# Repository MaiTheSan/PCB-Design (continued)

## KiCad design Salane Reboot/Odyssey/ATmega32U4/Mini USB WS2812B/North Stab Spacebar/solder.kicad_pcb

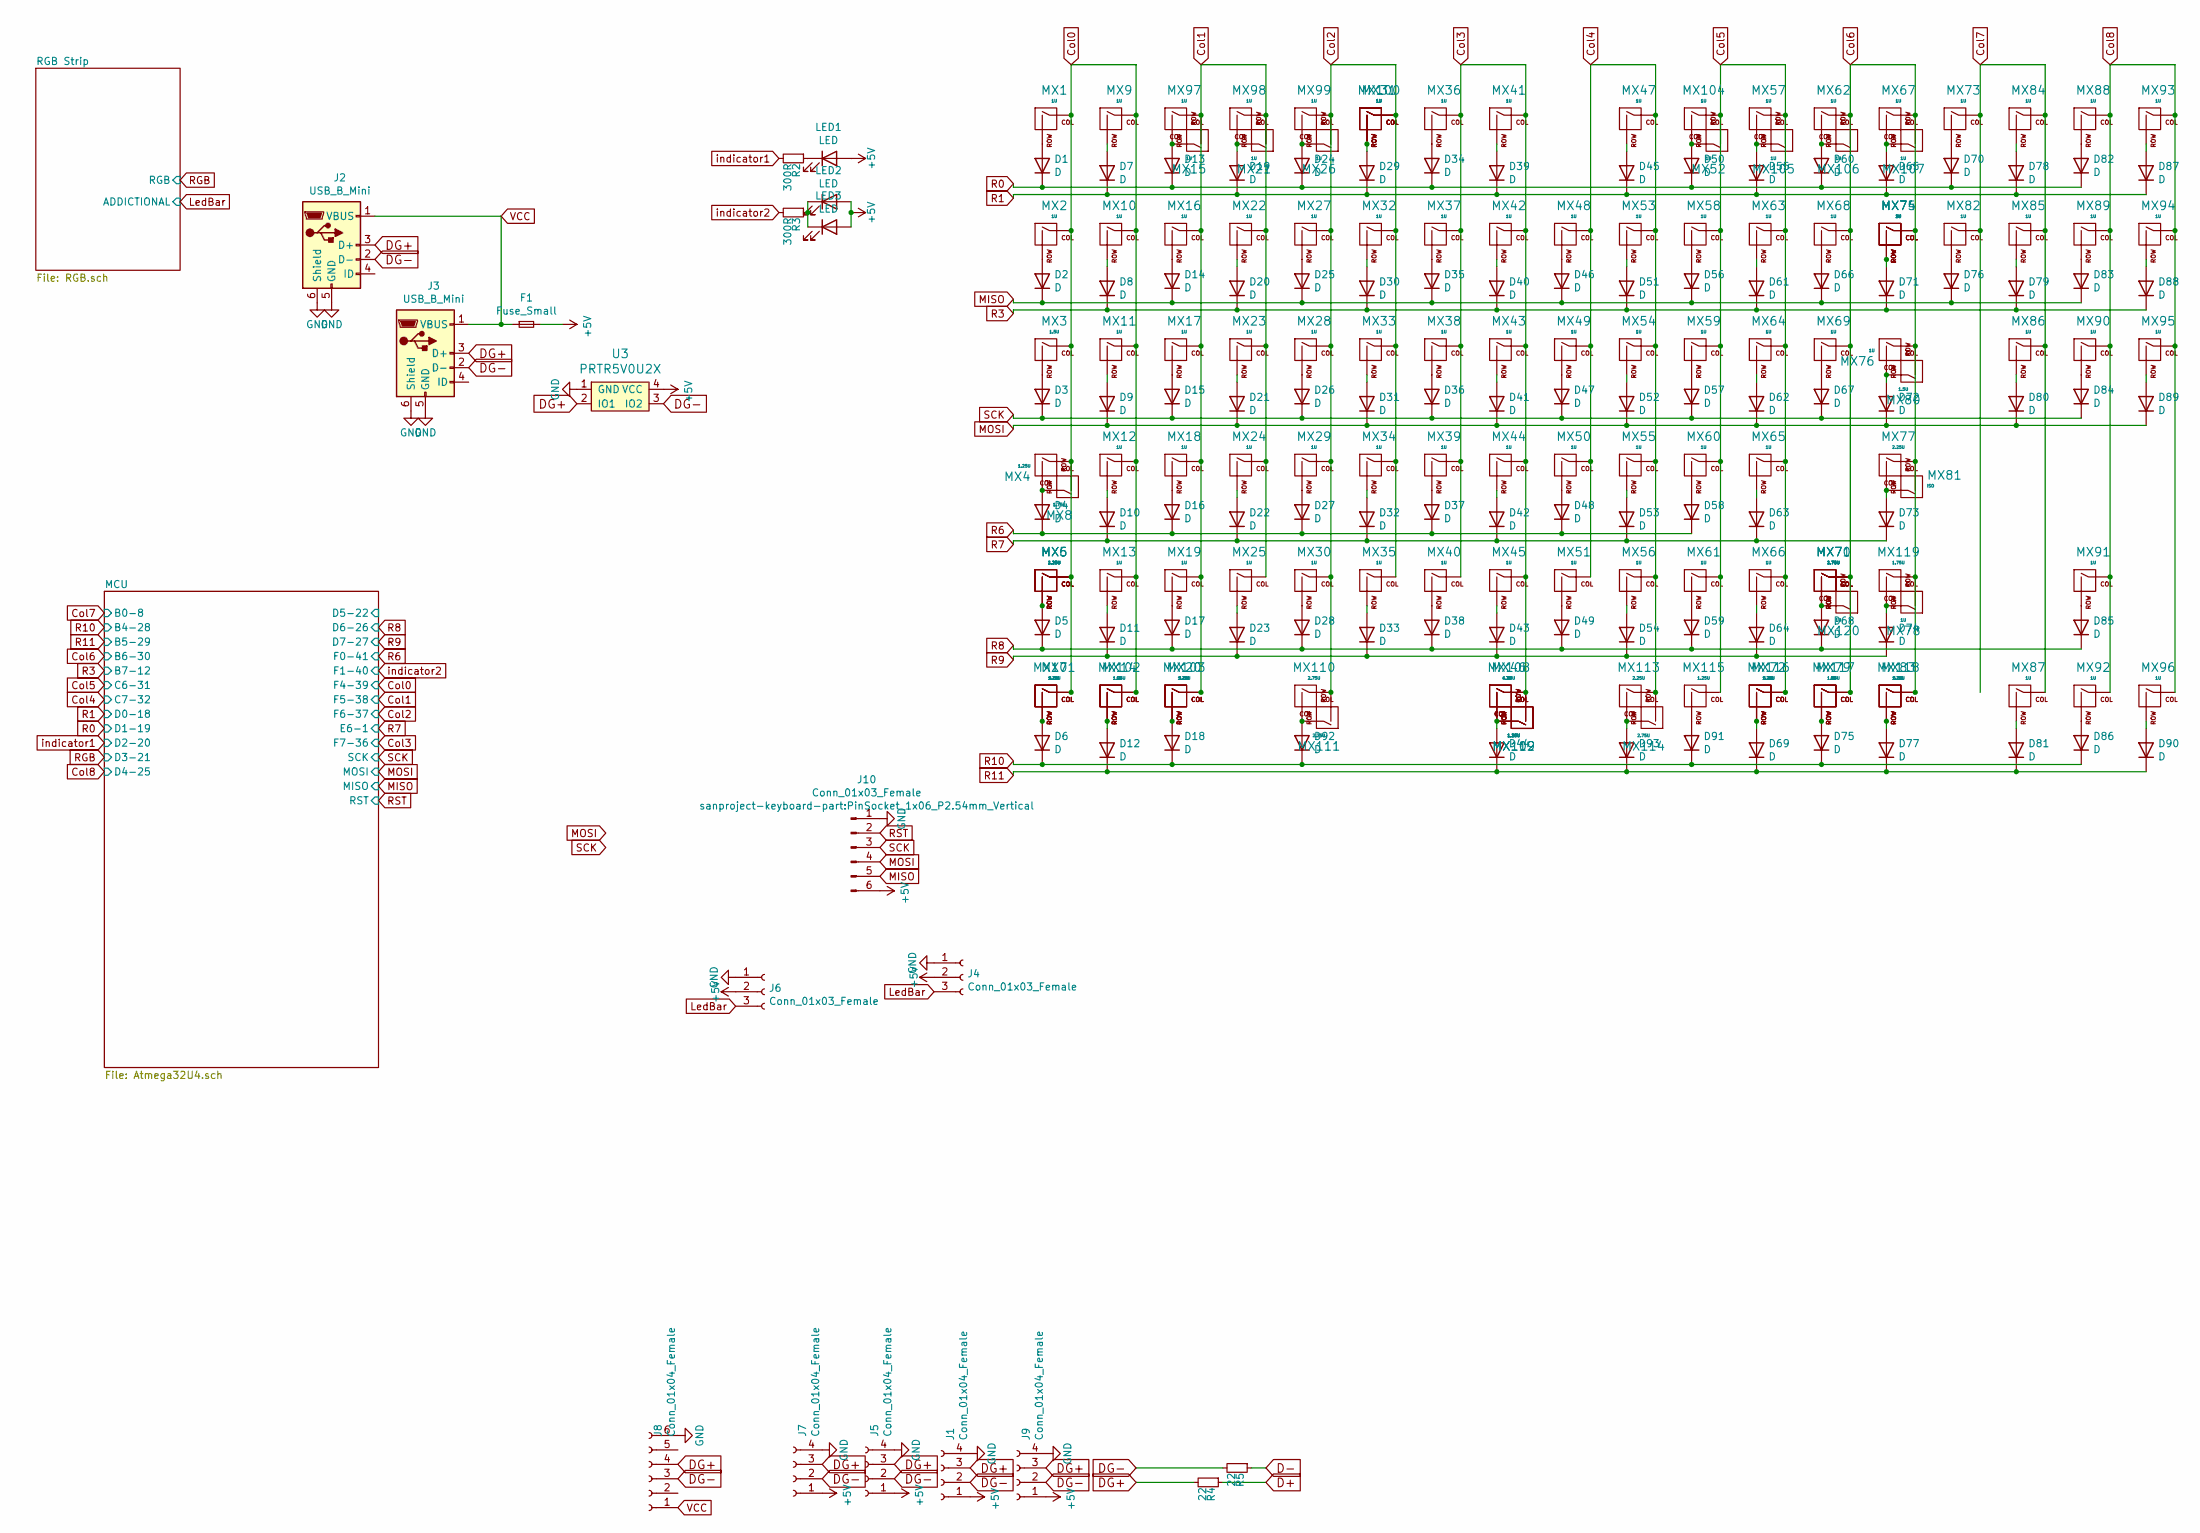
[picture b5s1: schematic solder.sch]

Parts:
D1, D2, D3, D4, D5, D6, D7, D8, D9, D10, D11, D12, D13, D14, D15, D16, D17, D18, D19, D20, D21, D22, D23, D24, D25, D26, D27, D28, D29, D30, D31, D32, D33, D34, D35, D36, D37, D38, D39, D40, D41, D42, D43, D44, D45, D46, D47, D48, D49, D50, D51, D52, D53, D54, D55, D56, D57, D58, D59, D60, D61, D62, D63, D64, D65, D66, D67, D68, D69, D70, D71, D72, D73, D74, D75, D76, D77, D78, D79, D80, D81, D82, D83, D84, D85, D86, D87, D88, D89, D90, D91, D92, D93: D; DIODE_1206_SawnsProjects
F1: Fuse_Small; Fuse_SMD1206_Reflow
J1, J7, J9: Conn_01x04_Female; JST-SR-4
J2, J3: USB_B_Mini; Molex-0548190589
J4: Conn_01x03_Female; PinSocket_1x03_P2.54mm_Vertical
J5: Conn_01x04_Female; PinHeader_1x04_P1.27mm_Vertical
J6: Conn_01x03_Female; JST-SR-3
J8: Conn_01x04_Female; BreakoutUSB
J10: Conn_01x03_Female; PinSocket_1x06_P2.54mm_Vertical
LED1, LED3: LED; MXOnly-LEDONLY-FLIPPED
LED2: LED; MXOnly-LEDONLY
MX1, MX2, MX9, MX10, MX11, MX12, MX13, MX14, MX15, MX16, MX17, MX18, MX19, MX21, MX22, MX23, MX24, MX25, MX26, MX27, MX28, MX29, MX30, MX31, MX32, MX33, MX34, MX35, MX36, MX37, MX38, MX39, MX40, MX41, MX42, MX43, MX44, MX45, MX47, MX48, MX49, MX50, MX51, MX52, MX53, MX54, MX55, MX56, MX57, MX58, MX59, MX60, MX61, MX62, MX63, MX64, MX65, MX66, MX67, MX68, MX69, MX73, MX74, MX76, MX78, MX79, MX82, MX84, MX85, MX86, MX87, MX88, MX89, MX90, MX91, MX92, MX93, MX94, MX95, MX96, MX97, MX98, MX99, MX100, MX104, MX105, MX106, MX107, MX120: 1U; MXOnly-1U-NoLED
MX3, MX7, MX20, MX72, MX80, MX83: 1.5U; MXOnly-1.5U-NoLED
MX4, MX5, MX101, MX102, MX103, MX109, MX112, MX115, MX116, MX117, MX118: 1.25U; MXOnly-1.25U-NoLED
MX6: 2.25U; MXOnly-2.25U-NoLED
MX8, MX70, MX119: 1.75U; MXOnly-1.75U-NoLED
MX46: 7U; MXOnly-7U-ReversedStabilizers-NoLED
MX71: 2.75U; MXOnly-2.75U-NoLED
MX75: 2U; MXOnly-2U-NoLED
MX77, MX111, MX113: 2.25U; MXOnly-2.25U-ReversedStabilizers-NoLED
MX81: ISO; MXOnly-ISO-ROTATED-ReversedStabilizers-NoLED
MX108: 6.25U; MXOnly-6.25U-ReversedStabilizers-NoLED
MX110, MX114: 2.75U; MXOnly-2.75U-ReversedStabilizers-NoLED
R2, R3: 300R; R_0805
R4, R5: 22; R_0603
U3: PRTR5V0U2X; SOT143B

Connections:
+5V: F1.2, J1.1, J4.2, J5.1, J6.2, J7.1, J9.1, J10.6, LED1.2 (A), LED2.2 (A), LED3.2 (A), U3.4 (VCC); also elsewhere on the board
Col0: MX1.1 (COL), MX2.1 (COL), MX3.1 (COL), MX4.1 (COL), MX5.1 (COL), MX6.1 (COL), MX7.1 (COL), MX8.2 (ROW), MX9.1 (COL), MX10.1 (COL), MX11.1 (COL), MX12.1 (COL), MX13.1 (COL), MX14.1 (COL), MX101.1 (COL), MX102.1 (COL); also elsewhere on the board
Col1: MX15.2 (ROW), MX16.1 (COL), MX17.1 (COL), MX18.1 (COL), MX19.1 (COL), MX20.1 (COL), MX21.2 (ROW), MX22.1 (COL), MX23.1 (COL), MX24.1 (COL), MX25.1 (COL), MX97.1 (COL), MX98.1 (COL), MX103.1 (COL); also elsewhere on the board
Col2: MX26.2 (ROW), MX27.1 (COL), MX28.1 (COL), MX29.1 (COL), MX30.1 (COL), MX31.1 (COL), MX32.1 (COL), MX33.1 (COL), MX34.1 (COL), MX35.1 (COL), MX99.1 (COL), MX100.1 (COL), MX110.1 (COL), MX111.2 (ROW); also elsewhere on the board
Col3: MX36.1 (COL), MX37.1 (COL), MX38.1 (COL), MX39.1 (COL), MX40.1 (COL), MX41.1 (COL), MX42.1 (COL), MX43.1 (COL), MX44.1 (COL), MX45.1 (COL), MX46.1 (COL), MX108.1 (COL), MX109.2 (ROW), MX112.2 (ROW); also elsewhere on the board
Col4: MX47.1 (COL), MX48.1 (COL), MX49.1 (COL), MX50.1 (COL), MX51.1 (COL), MX53.1 (COL), MX54.1 (COL), MX55.1 (COL), MX56.1 (COL), MX113.1 (COL), MX114.2 (ROW); also elsewhere on the board
Col5: MX52.2 (ROW), MX57.1 (COL), MX58.1 (COL), MX59.1 (COL), MX60.1 (COL), MX61.1 (COL), MX63.1 (COL), MX64.1 (COL), MX65.1 (COL), MX66.1 (COL), MX72.1 (COL), MX104.1 (COL), MX105.2 (ROW), MX115.1 (COL), MX116.1 (COL); also elsewhere on the board
Col6: MX62.1 (COL), MX67.1 (COL), MX68.1 (COL), MX69.1 (COL), MX70.1 (COL), MX71.1 (COL), MX74.1 (COL), MX75.1 (COL), MX76.1 (COL), MX77.1 (COL), MX78.2 (ROW), MX79.1 (COL), MX80.2 (ROW), MX81.2 (ROW), MX83.1 (COL), MX106.2 (ROW), MX107.2 (ROW), MX117.1 (COL), MX118.1 (COL), MX119.1 (COL), MX120.2 (ROW); also elsewhere on the board
Col7: MX73.1 (COL), MX82.1 (COL), MX84.1 (COL), MX85.1 (COL), MX86.1 (COL), MX87.1 (COL); also elsewhere on the board
Col8: MX88.1 (COL), MX89.1 (COL), MX90.1 (COL), MX91.1 (COL), MX92.1 (COL), MX93.1 (COL), MX94.1 (COL), MX95.1 (COL), MX96.1 (COL); also elsewhere on the board
D+: R4.1; also elsewhere on the board
D-: R5.1; also elsewhere on the board
DG+: J1.3, J2.3 (D+), J3.3 (D+), J5.3, J7.3, J8.4, J9.3, R4.2, U3.2 (IO1)
DG-: J1.2, J2.2 (D-), J3.2 (D-), J5.2, J7.2, J8.3, J9.2, R5.2, U3.3 (IO2)
GND: J1.4, J2.5 (GND), J2.6 (Shield), J3.5 (GND), J3.6 (Shield), J4.1, J5.4, J6.1, J7.4, J8.6, J9.4, J10.1, U3.1 (GND); also elsewhere on the board
LedBar: J4.3, J6.3; also elsewhere on the board
MISO: D2.1 (K), D14.1 (K), D25.1 (K), D35.1 (K), D46.1 (K), D56.1 (K), D66.1 (K), D76.1 (K), D83.1 (K), J10.5; also elsewhere on the board
MOSI: D9.1 (K), D21.1 (K), D31.1 (K), D41.1 (K), D52.1 (K), D62.1 (K), D72.1 (K), D80.1 (K), D89.1 (K), J10.4; also elsewhere on the board
unnamed: D1.2 (A), MX1.2 (ROW)
unnamed: D2.2 (A), MX2.2 (ROW)
unnamed: D3.2 (A), MX3.2 (ROW)
unnamed: D4.2 (A), MX4.2 (ROW), MX8.1 (COL)
unnamed: D5.2 (A), MX5.2 (ROW), MX6.2 (ROW)
unnamed: D6.2 (A), MX7.2 (ROW), MX101.2 (ROW)
unnamed: D7.2 (A), MX9.2 (ROW)
unnamed: D8.2 (A), MX10.2 (ROW)
unnamed: D9.2 (A), MX11.2 (ROW)
unnamed: D10.2 (A), MX12.2 (ROW)
unnamed: D11.2 (A), MX13.2 (ROW)
unnamed: D12.2 (A), MX14.2 (ROW), MX102.2 (ROW)
unnamed: D13.2 (A), MX15.1 (COL), MX97.2 (ROW)
unnamed: D14.2 (A), MX16.2 (ROW)
unnamed: D15.2 (A), MX17.2 (ROW)
unnamed: D16.2 (A), MX18.2 (ROW)
unnamed: D17.2 (A), MX19.2 (ROW)
unnamed: D18.2 (A), MX20.2 (ROW), MX103.2 (ROW)
unnamed: D19.2 (A), MX21.1 (COL), MX98.2 (ROW)
unnamed: D20.2 (A), MX22.2 (ROW)
unnamed: D21.2 (A), MX23.2 (ROW)
unnamed: D22.2 (A), MX24.2 (ROW)
unnamed: D23.2 (A), MX25.2 (ROW)
unnamed: D24.2 (A), MX26.1 (COL), MX99.2 (ROW)
unnamed: D25.2 (A), MX27.2 (ROW)
unnamed: D26.2 (A), MX28.2 (ROW)
unnamed: D27.2 (A), MX29.2 (ROW)
unnamed: D28.2 (A), MX30.2 (ROW)
unnamed: D29.2 (A), MX31.2 (ROW), MX100.2 (ROW)
unnamed: D30.2 (A), MX32.2 (ROW)
unnamed: D31.2 (A), MX33.2 (ROW)
unnamed: D32.2 (A), MX34.2 (ROW)
unnamed: D33.2 (A), MX35.2 (ROW)
unnamed: D34.2 (A), MX36.2 (ROW)
unnamed: D35.2 (A), MX37.2 (ROW)
unnamed: D36.2 (A), MX38.2 (ROW)
unnamed: D37.2 (A), MX39.2 (ROW)
unnamed: D38.2 (A), MX40.2 (ROW)
unnamed: D39.2 (A), MX41.2 (ROW)
unnamed: D40.2 (A), MX42.2 (ROW)
unnamed: D41.2 (A), MX43.2 (ROW)
unnamed: D42.2 (A), MX44.2 (ROW)
unnamed: D43.2 (A), MX45.2 (ROW)
unnamed: D44.2 (A), MX46.2 (ROW), MX108.2 (ROW), MX109.1 (COL), MX112.1 (COL)
unnamed: D45.2 (A), MX47.2 (ROW)
unnamed: D46.2 (A), MX48.2 (ROW)
unnamed: D47.2 (A), MX49.2 (ROW)
unnamed: D48.2 (A), MX50.2 (ROW)
unnamed: D49.2 (A), MX51.2 (ROW)
unnamed: D50.2 (A), MX52.1 (COL), MX104.2 (ROW)
unnamed: D51.2 (A), MX53.2 (ROW)
unnamed: D52.2 (A), MX54.2 (ROW)
unnamed: D53.2 (A), MX55.2 (ROW)
unnamed: D54.2 (A), MX56.2 (ROW)
unnamed: D55.2 (A), MX57.2 (ROW), MX105.1 (COL)
unnamed: D56.2 (A), MX58.2 (ROW)
unnamed: D57.2 (A), MX59.2 (ROW)
unnamed: D58.2 (A), MX60.2 (ROW)
unnamed: D59.2 (A), MX61.2 (ROW)
unnamed: D60.2 (A), MX62.2 (ROW), MX106.1 (COL)
unnamed: D61.2 (A), MX63.2 (ROW)
unnamed: D62.2 (A), MX64.2 (ROW)
unnamed: D63.2 (A), MX65.2 (ROW)
unnamed: D64.2 (A), MX66.2 (ROW)
unnamed: D65.2 (A), MX67.2 (ROW), MX107.1 (COL)
unnamed: D66.2 (A), MX68.2 (ROW)
unnamed: D67.2 (A), MX69.2 (ROW)
unnamed: D68.2 (A), MX70.2 (ROW), MX71.2 (ROW), MX120.1 (COL)
unnamed: D69.2 (A), MX72.2 (ROW), MX116.2 (ROW)
unnamed: D70.2 (A), MX73.2 (ROW)
unnamed: D71.2 (A), MX74.2 (ROW), MX75.2 (ROW)
unnamed: D72.2 (A), MX76.2 (ROW), MX80.1 (COL)
unnamed: D73.2 (A), MX77.2 (ROW), MX81.1 (COL)
unnamed: D74.2 (A), MX78.1 (COL), MX119.2 (ROW)
unnamed: D75.2 (A), MX79.2 (ROW), MX117.2 (ROW)
unnamed: D76.2 (A), MX82.2 (ROW)
unnamed: D77.2 (A), MX83.2 (ROW), MX118.2 (ROW)
unnamed: D78.2 (A), MX84.2 (ROW)
unnamed: D79.2 (A), MX85.2 (ROW)
unnamed: D80.2 (A), MX86.2 (ROW)
unnamed: D81.2 (A), MX87.2 (ROW)
unnamed: D82.2 (A), MX88.2 (ROW)
unnamed: D83.2 (A), MX89.2 (ROW)
unnamed: D84.2 (A), MX90.2 (ROW)
unnamed: D85.2 (A), MX91.2 (ROW)
unnamed: D86.2 (A), MX92.2 (ROW)
unnamed: D87.2 (A), MX93.2 (ROW)
unnamed: D88.2 (A), MX94.2 (ROW)
unnamed: D89.2 (A), MX95.2 (ROW)
unnamed: D90.2 (A), MX96.2 (ROW)
unnamed: D91.2 (A), MX115.2 (ROW)
unnamed: D92.2 (A), MX110.2 (ROW), MX111.1 (COL)
unnamed: D93.2 (A), MX113.2 (ROW), MX114.1 (COL)
unnamed: LED1.1 (K), R2.1
unnamed: LED2.1 (K), LED3.1 (K), R3.1
R0: D1.1 (K), D13.1 (K), D24.1 (K), D34.1 (K), D50.1 (K), D60.1 (K), D70.1 (K), D82.1 (K); also elsewhere on the board
R1: D7.1 (K), D19.1 (K), D29.1 (K), D39.1 (K), D45.1 (K), D55.1 (K), D65.1 (K), D78.1 (K), D87.1 (K); also elsewhere on the board
R3: D8.1 (K), D20.1 (K), D30.1 (K), D40.1 (K), D51.1 (K), D61.1 (K), D71.1 (K), D79.1 (K), D88.1 (K); also elsewhere on the board
R6: D4.1 (K), D16.1 (K), D27.1 (K), D37.1 (K), D48.1 (K), D58.1 (K); also elsewhere on the board
R7: D10.1 (K), D22.1 (K), D32.1 (K), D42.1 (K), D53.1 (K), D63.1 (K), D73.1 (K); also elsewhere on the board
R8: D5.1 (K), D17.1 (K), D28.1 (K), D38.1 (K), D49.1 (K), D59.1 (K), D68.1 (K), D85.1 (K); also elsewhere on the board
R9: D11.1 (K), D23.1 (K), D33.1 (K), D43.1 (K), D54.1 (K), D64.1 (K), D74.1 (K); also elsewhere on the board
R10: D6.1 (K), D18.1 (K), D75.1 (K), D86.1 (K), D91.1 (K), D92.1 (K); also elsewhere on the board
R11: D12.1 (K), D44.1 (K), D69.1 (K), D77.1 (K), D81.1 (K), D90.1 (K), D93.1 (K); also elsewhere on the board
RST: J10.2; also elsewhere on the board
SCK: D3.1 (K), D15.1 (K), D26.1 (K), D36.1 (K), D47.1 (K), D57.1 (K), D67.1 (K), D84.1 (K), J10.3; also elsewhere on the board
VCC: F1.1, J2.1 (VBUS), J3.1 (VBUS), J8.1; also elsewhere on the board
indicator1: R2.2; also elsewhere on the board
indicator2: R3.2; also elsewhere on the board

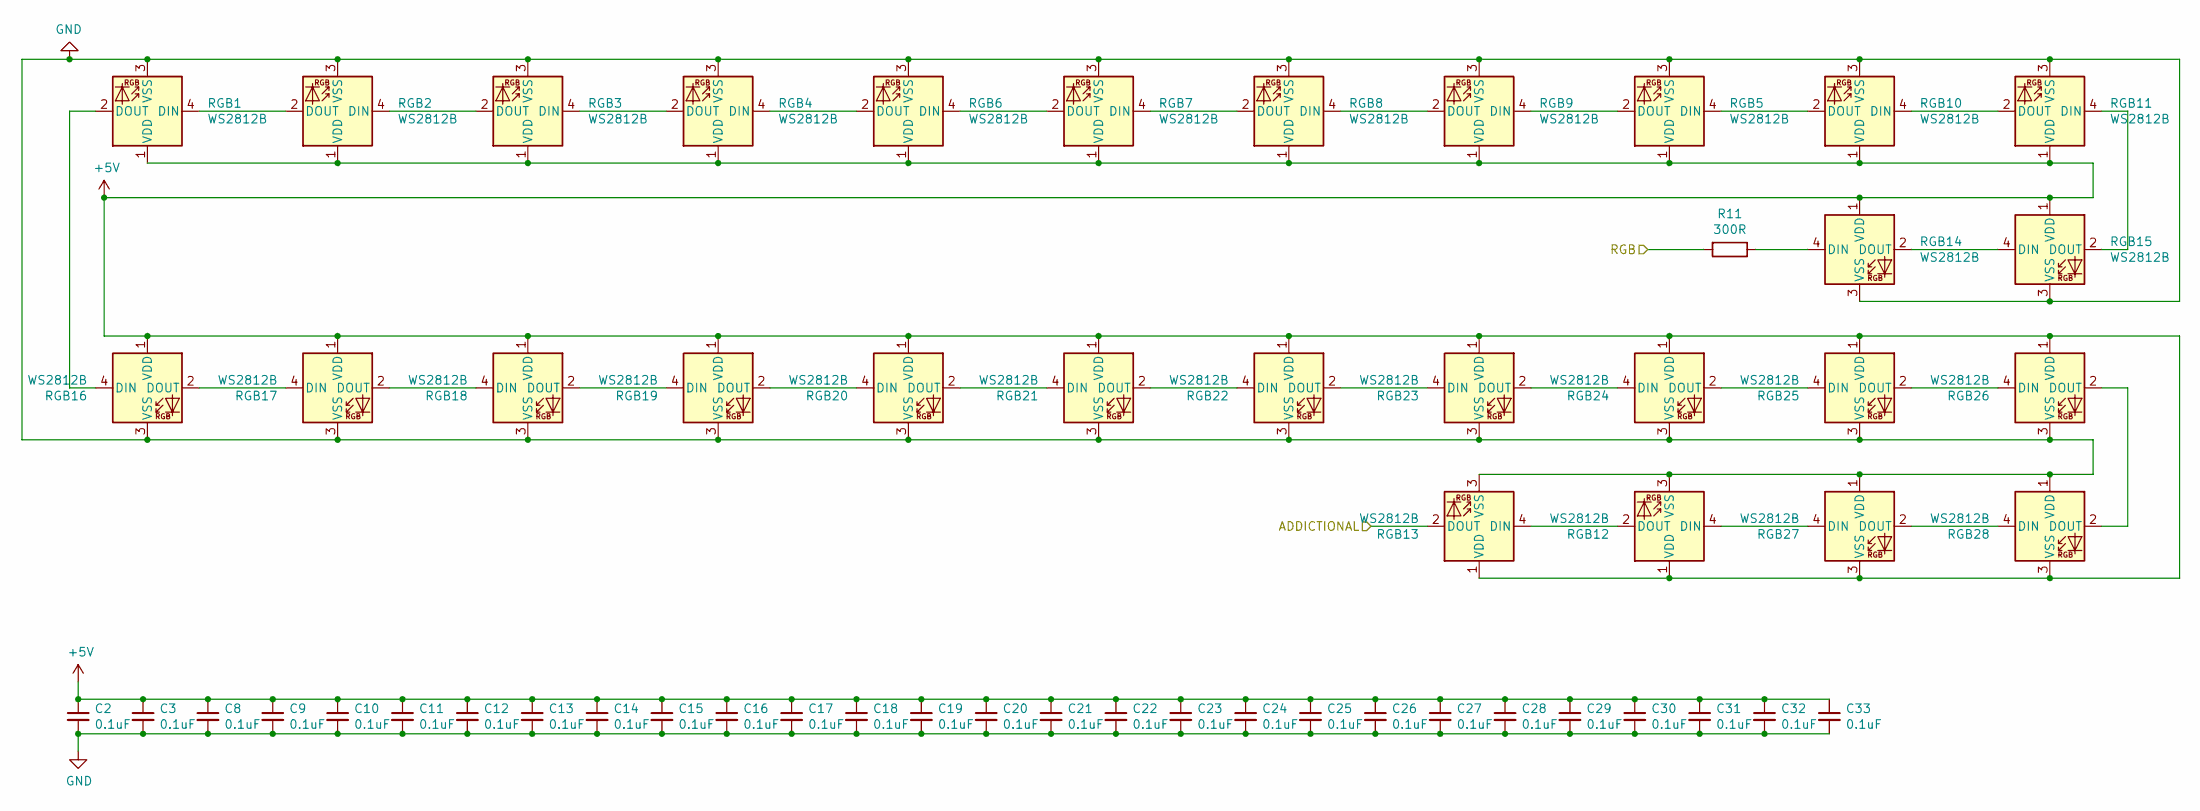
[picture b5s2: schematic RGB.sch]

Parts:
C2, C3, C8, C9, C10, C11, C12, C13, C14, C15, C16, C17, C18, C19, C20, C21, C22, C23, C24, C25, C26, C27, C28, C29, C30, C31, C32, C33: 0.1uF; C_0603
R11: 300R; R_0805
RGB1, RGB2, RGB3, RGB4, RGB5, RGB6, RGB7, RGB8, RGB9, RGB10, RGB11, RGB12, RGB13, RGB14, RGB15, RGB16, RGB17, RGB18, RGB19, RGB20, RGB21, RGB22, RGB23, RGB24, RGB25, RGB26, RGB27, RGB28: WS2812B; LED_WS2812B_PLCC4_5.0x5.0mm_P3.2mm

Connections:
+5V: C2.1, C3.1, C8.1, C9.1, C10.1, C11.1, C12.1, C13.1, C14.1, C15.1, C16.1, C17.1, C18.1, C19.1, C20.1, C21.1, C22.1, C23.1, C24.1, C25.1, C26.1, C27.1, C28.1, C29.1, C30.1, C31.1, C32.1, C33.1, RGB1.1 (VDD), RGB2.1 (VDD), RGB3.1 (VDD), RGB4.1 (VDD), RGB5.1 (VDD), RGB6.1 (VDD), RGB7.1 (VDD), RGB8.1 (VDD), RGB9.1 (VDD), RGB10.1 (VDD), RGB11.1 (VDD), RGB12.1 (VDD), RGB13.1 (VDD), RGB14.1 (VDD), RGB15.1 (VDD), RGB16.1 (VDD), RGB17.1 (VDD), RGB18.1 (VDD), RGB19.1 (VDD), RGB20.1 (VDD), RGB21.1 (VDD), RGB22.1 (VDD), RGB23.1 (VDD), RGB24.1 (VDD), RGB25.1 (VDD), RGB26.1 (VDD), RGB27.3 (VSS), RGB28.3 (VSS); also elsewhere on the board
GND: C2.2, C3.2, C8.2, C9.2, C10.2, C11.2, C12.2, C13.2, C14.2, C15.2, C16.2, C17.2, C18.2, C19.2, C20.2, C21.2, C22.2, C23.2, C24.2, C25.2, C26.2, C27.2, C28.2, C29.2, C30.2, C31.2, C32.2, C33.2, RGB1.3 (VSS), RGB2.3 (VSS), RGB3.3 (VSS), RGB4.3 (VSS), RGB5.3 (VSS), RGB6.3 (VSS), RGB7.3 (VSS), RGB8.3 (VSS), RGB9.3 (VSS), RGB10.3 (VSS), RGB11.3 (VSS), RGB12.3 (VSS), RGB13.3 (VSS), RGB14.3 (VSS), RGB15.3 (VSS), RGB16.3 (VSS), RGB17.3 (VSS), RGB18.3 (VSS), RGB19.3 (VSS), RGB20.3 (VSS), RGB21.3 (VSS), RGB22.3 (VSS), RGB23.3 (VSS), RGB24.3 (VSS), RGB25.3 (VSS), RGB26.3 (VSS), RGB27.1 (VDD), RGB28.1 (VDD); also elsewhere on the board
LedBar: RGB13.2 (DOUT); also elsewhere on the board
unnamed: R11.1, RGB14.4 (DIN)
unnamed: RGB1.2 (DOUT), RGB16.4 (DIN)
unnamed: RGB1.4 (DIN), RGB2.2 (DOUT)
unnamed: RGB2.4 (DIN), RGB3.2 (DOUT)
unnamed: RGB3.4 (DIN), RGB4.2 (DOUT)
unnamed: RGB4.4 (DIN), RGB6.2 (DOUT)
unnamed: RGB5.2 (DOUT), RGB9.4 (DIN)
unnamed: RGB6.4 (DIN), RGB7.2 (DOUT)
unnamed: RGB7.4 (DIN), RGB8.2 (DOUT)
unnamed: RGB8.4 (DIN), RGB9.2 (DOUT)
unnamed: RGB5.4 (DIN), RGB10.2 (DOUT)
unnamed: RGB10.4 (DIN), RGB11.2 (DOUT)
unnamed: RGB11.4 (DIN), RGB15.2 (DOUT)
unnamed: RGB12.2 (DOUT), RGB13.4 (DIN)
unnamed: RGB12.4 (DIN), RGB27.4 (DIN)
unnamed: RGB14.2 (DOUT), RGB15.4 (DIN)
unnamed: RGB16.2 (DOUT), RGB17.4 (DIN)
unnamed: RGB17.2 (DOUT), RGB18.4 (DIN)
unnamed: RGB18.2 (DOUT), RGB19.4 (DIN)
unnamed: RGB19.2 (DOUT), RGB20.4 (DIN)
unnamed: RGB20.2 (DOUT), RGB21.4 (DIN)
unnamed: RGB21.2 (DOUT), RGB22.4 (DIN)
unnamed: RGB22.2 (DOUT), RGB23.4 (DIN)
unnamed: RGB23.2 (DOUT), RGB24.4 (DIN)
unnamed: RGB24.2 (DOUT), RGB25.4 (DIN)
unnamed: RGB25.2 (DOUT), RGB26.4 (DIN)
unnamed: RGB26.2 (DOUT), RGB28.2 (DOUT)
unnamed: RGB27.2 (DOUT), RGB28.4 (DIN)
RGB: R11.2; also elsewhere on the board

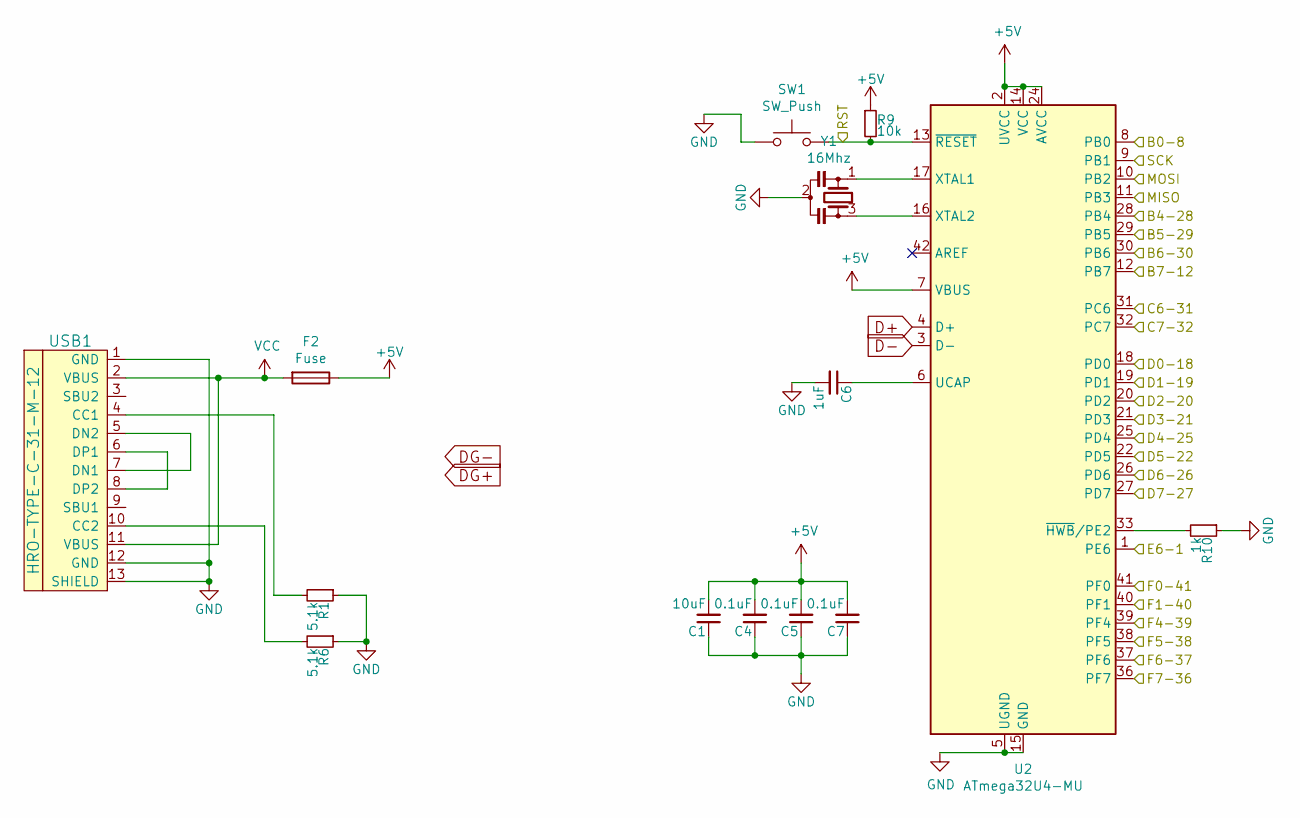
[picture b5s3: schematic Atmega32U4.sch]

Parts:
C1: 10uF; C_0603
C4, C5, C7: 0.1uF; C_0603
C6: 1uF; C_0603
F2: Fuse; Fuse_SMD1206_Reflow
R1, R6: 5.1k; R_0805
R9: 10k; R_0805
R10: 1k; R_0603
SW1: SW_Push; SKQG-1155865-2pin
U2: ATmega32U4-MU; QFN-44-1EP_7x7mm_P0.5mm_EP5.15x5.15mm
USB1: HRO-TYPE-C-31-M-12; HRO-TYPE-C-31-M-12-Assembly
Y1: 16Mhz; Resonator_SMD_muRata_CSTxExxV-3Pin_3.0x1.1mm

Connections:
+5V: C1.2, C4.2, C5.2, C7.2, F2.1, R9.1, U2.2 (UVCC), U2.7 (VBUS), U2.14 (VCC), U2.24 (AVCC), U2.34 (VCC), U2.44 (AVCC); also elsewhere on the board
/MCU/D5-22: U2.22 (PD5)
Col0: U2.39 (PF4); also elsewhere on the board
Col1: U2.38 (PF5); also elsewhere on the board
Col2: U2.37 (PF6); also elsewhere on the board
Col3: U2.36 (PF7); also elsewhere on the board
Col4: U2.32 (PC7); also elsewhere on the board
Col5: U2.31 (PC6); also elsewhere on the board
Col6: U2.30 (PB6); also elsewhere on the board
Col7: U2.8 (PB0); also elsewhere on the board
Col8: U2.25 (PD4); also elsewhere on the board
D+: U2.4 (D+); also elsewhere on the board
D-: U2.3 (D-); also elsewhere on the board
GND: C1.1, C4.1, C5.1, C6.2, C7.1, R1.1, R6.1, R10.1, SW1.1, U2.5 (UGND), U2.15 (GND), U2.23 (GND), U2.35 (GND), U2.43 (GND), U2.45 (GND), USB1.1 (GND), USB1.12 (GND), USB1.13 (SHIELD), Y1.2; also elsewhere on the board
MISO: U2.11 (PB3); also elsewhere on the board
MOSI: U2.10 (PB2); also elsewhere on the board
unnamed: C6.1, U2.6 (UCAP)
unnamed: R1.2, USB1.4 (CC1)
unnamed: R6.2, USB1.10 (CC2)
unnamed: R10.2, U2.33 (~HWB~/PE2)
unnamed: U2.16 (XTAL2), Y1.3
unnamed: U2.17 (XTAL1), Y1.1
unnamed: USB1.5 (DN2), USB1.7 (DN1)
unnamed: USB1.6 (DP1), USB1.8 (DP2)
R0: U2.19 (PD1); also elsewhere on the board
R1: U2.18 (PD0); also elsewhere on the board
R3: U2.12 (PB7); also elsewhere on the board
R6: U2.41 (PF0); also elsewhere on the board
R7: U2.1 (PE6); also elsewhere on the board
R8: U2.26 (PD6); also elsewhere on the board
R9: U2.27 (PD7); also elsewhere on the board
R10: U2.28 (PB4); also elsewhere on the board
R11: U2.29 (PB5); also elsewhere on the board
RGB: U2.21 (PD3); also elsewhere on the board
RST: R9.2, SW1.2, U2.13 (~RESET); also elsewhere on the board
SCK: U2.9 (PB1); also elsewhere on the board
VCC: F2.2, USB1.2 (VBUS), USB1.11 (VBUS); also elsewhere on the board
indicator1: U2.20 (PD2); also elsewhere on the board
indicator2: U2.40 (PF1); also elsewhere on the board

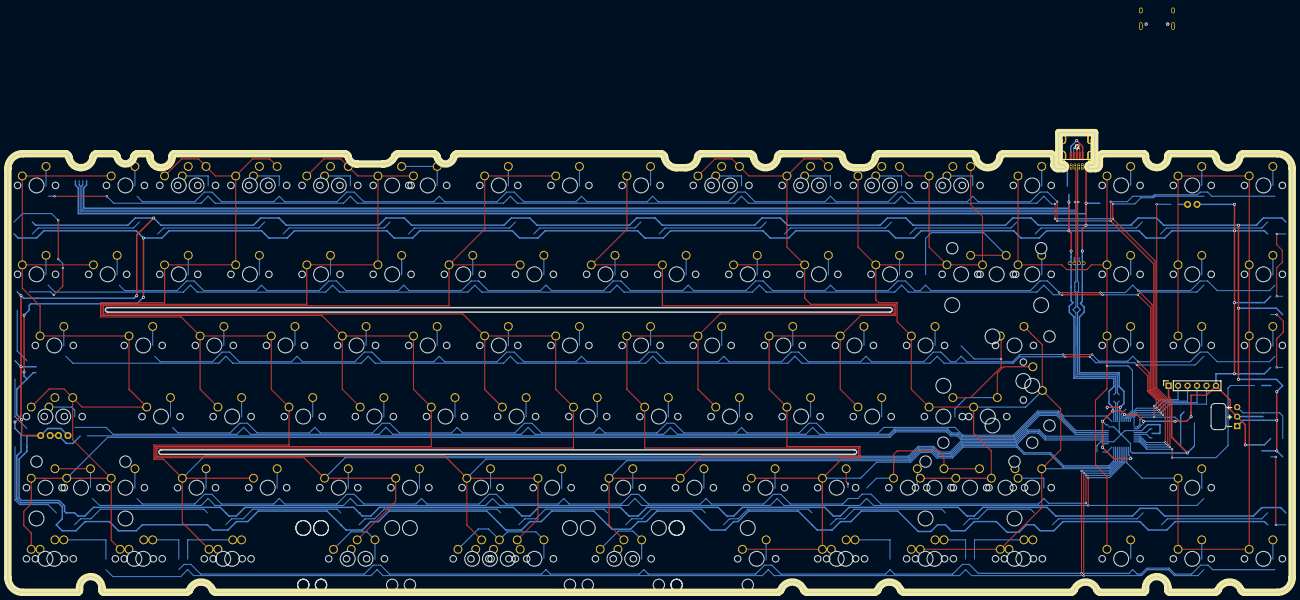
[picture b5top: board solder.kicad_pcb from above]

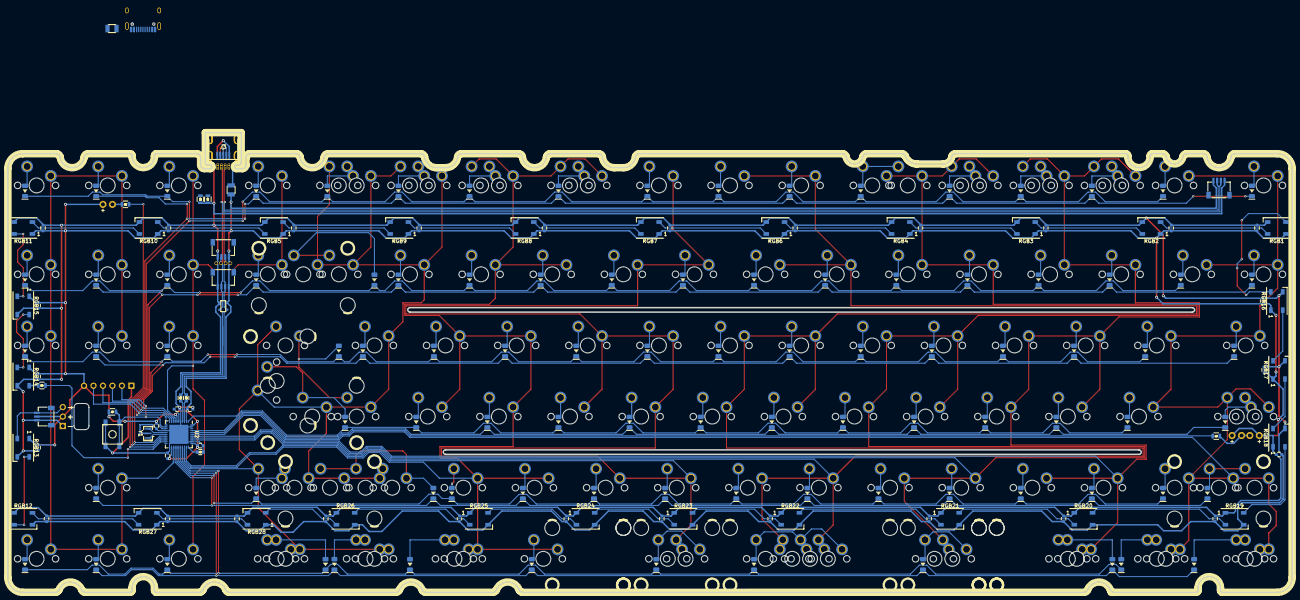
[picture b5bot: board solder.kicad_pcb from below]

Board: 2 copper layers, 344.0 x 123.1 mm, 303 parts (175 on the bottom side), 164 nets.
